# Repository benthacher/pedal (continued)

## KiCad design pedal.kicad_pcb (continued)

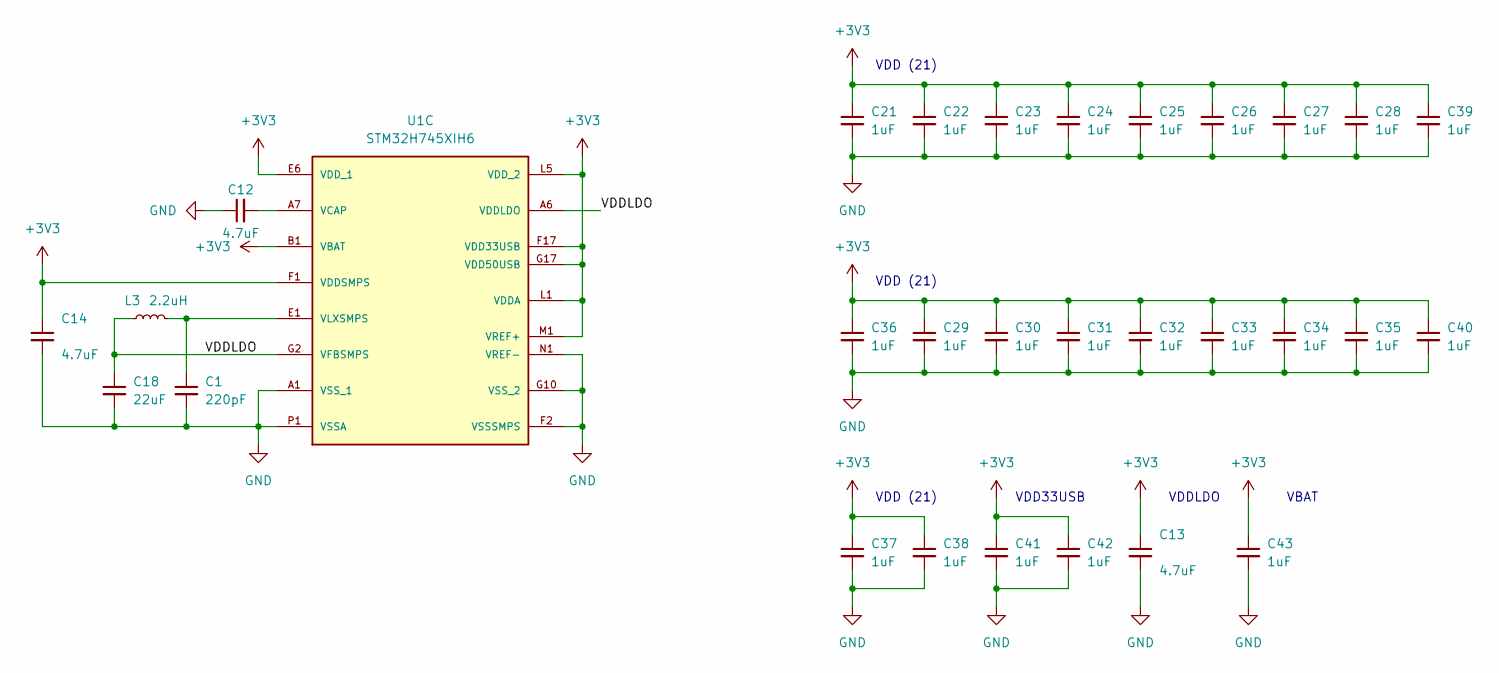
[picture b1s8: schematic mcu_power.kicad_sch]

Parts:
C1: 220pF; C_0402_1005Metric; Voltage 50V; LCSC C1530
C12, C13, C14: 4.7uF; C_0402_1005Metric; LCSC C23733
C18: 22uF; C_0805_2012Metric; Voltage 25V; LCSC C45783
C21, C22, C23, C24, C25, C26, C27, C28, C29, C30, C31, C32, C33, C34, C35, C36, C37, C38, C39, C40, C41, C42, C43: 1uF; C_0402_1005Metric; voltage 25; LCSC C52923
L3: 2.2uH; L_0805_2012Metric; LCSC C49435080
U1: STM32H745XIH6; BGA265C80P17X17_1400X1400X120; PARTREV 3; LCSC C1338373

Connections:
+3V3: C13.1, C14.1, C21.1, C22.1, C23.1, C24.1, C25.1, C26.1, C27.1, C28.1, C29.1, C30.1, C31.1, C32.1, C33.1, C34.1, C35.1, C36.1, C37.1, C38.1, C39.1, C40.1, C41.1, C42.1, C43.1, U1.B1 (VBAT), U1.E6 (VDD_1), U1.E9 (VDD_1), U1.E11 (VDD_1), U1.F1 (VDDSMPS), U1.F5 (VDD_1), U1.F17 (VDD33USB), U1.G5 (VDD_1), U1.G13 (VDD_1), U1.G17 (VDD50USB), U1.H5 (VDD_1), U1.H13 (VDD_1), U1.J13 (VDD_1), U1.K5 (VDD_1), U1.K13 (VDD_1), U1.L1 (VDDA), U1.L5 (VDD_2), U1.L13 (VDD_2), U1.M1 (VREF+), U1.M5 (VDD_2), U1.M13 (VDD_2), U1.N7 (VDD_2), U1.N8 (VDD_2), U1.N10 (VDD_2), U1.N11 (VDD_2), U1.N12 (VDD_2), U1.P17 (VDD_2); also elsewhere on the board
GND: C1.2, C12.1, C13.2, C14.2, C18.2, C21.2, C22.2, C23.2, C24.2, C25.2, C26.2, C27.2, C28.2, C29.2, C30.2, C31.2, C32.2, C33.2, C34.2, C35.2, C36.2, C37.2, C38.2, C39.2, C40.2, C41.2, C42.2, C43.2, U1.A1 (VSS_1), U1.A17 (VSS_1), U1.B2 (VSS_1), U1.B6 (VSS_1), U1.C10 (VSS_1), U1.C13 (VSS_1), U1.C16 (VSS_1), U1.F2 (VSSSMPS), U1.G7 (VSS_1), U1.G8 (VSS_1), U1.G9 (VSS_1), U1.G10 (VSS_2), U1.G11 (VSS_2), U1.G16 (VSS_1), U1.H7 (VSS_2), U1.H8 (VSS_2), U1.H9 (VSS_2), U1.H10 (VSS_2), U1.H11 (VSS_2), U1.J3 (VSS_1), U1.J7 (VSS_2), U1.J8 (VSS_2), U1.J9 (VSS_2), U1.J10 (VSS_2), U1.J11 (VSS_2), U1.J16 (VSS_1), U1.J17 (VSS_1), U1.K7 (VSS_2), U1.K8 (VSS_2), U1.K9 (VSS_2), U1.K10 (VSS_2), U1.K11 (VSS_2), U1.K15 (VSS_1), U1.L7 (VSS_2), U1.L8 (VSS_2), U1.L9 (VSS_2), U1.L10 (VSS_2), U1.L11 (VSS_2), U1.L15 (VSS_1), U1.M15 (VSS_1), U1.N1 (VREF-), U1.N16 (VSS_1), U1.P1 (VSSA), U1.R4 (VSS_1), U1.R8 (VSS_1), U1.T12 (VSS_1), U1.U1 (VSS_1), U1.U17 (VSS_1); also elsewhere on the board
unnamed: C1.1, L3.2, U1.E1 (VLXSMPS)
VCAP: C12.2, U1.A7 (VCAP), U1.D17 (VCAP), U1.U11 (VCAP)
VDDLDO: C18.1, L3.1, U1.A6 (VDDLDO), U1.C17 (VDDLDO), U1.G2 (VFBSMPS), U1.U12 (VDDLDO)

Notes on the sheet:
VDD33USB
VDD (21)
VDDLDO
VBAT

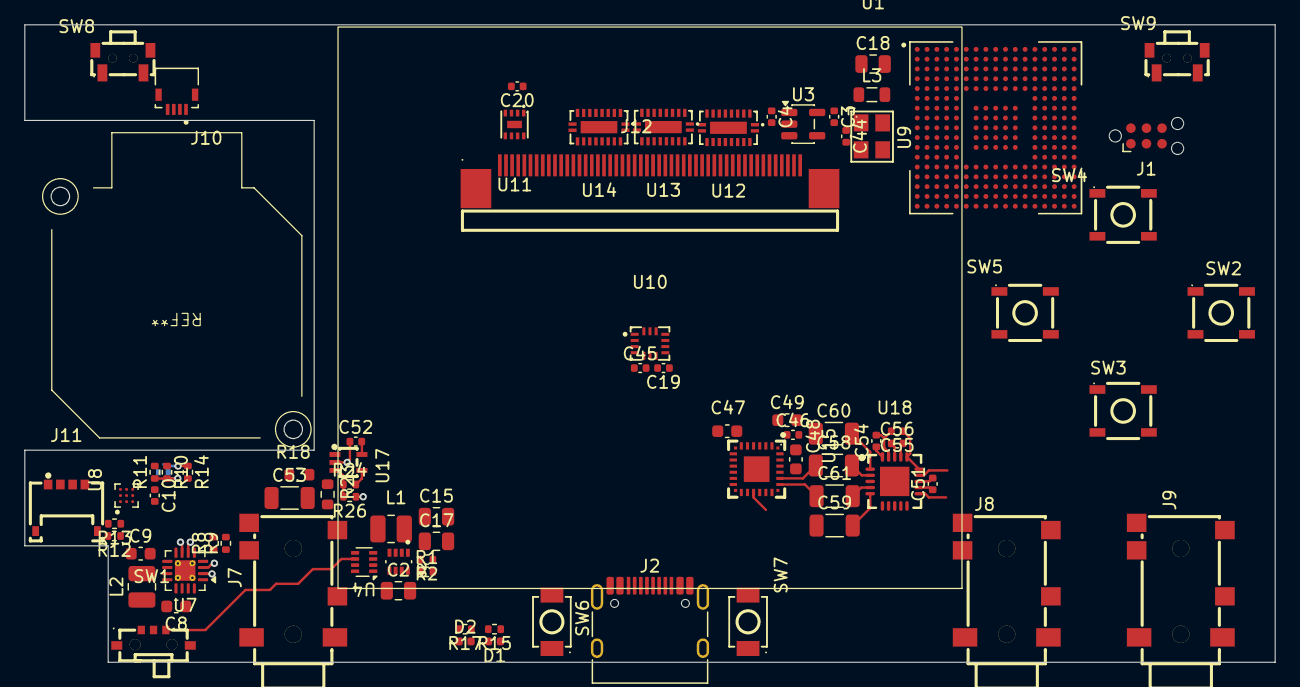
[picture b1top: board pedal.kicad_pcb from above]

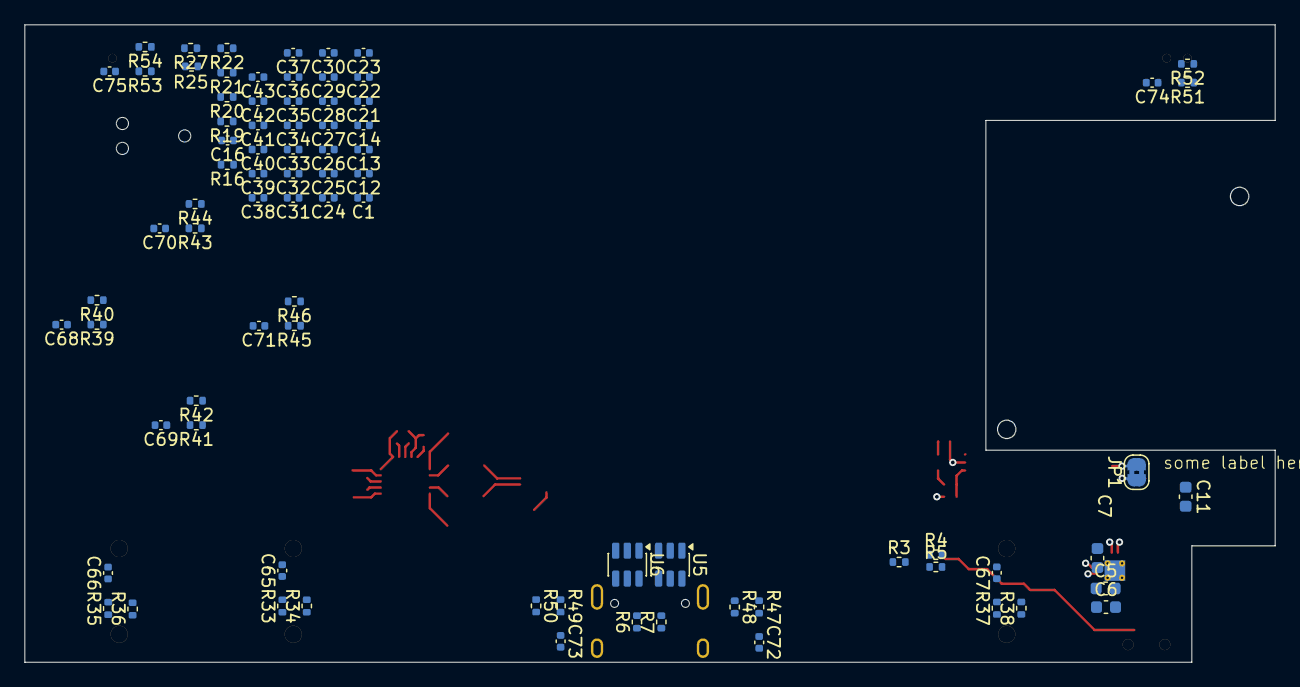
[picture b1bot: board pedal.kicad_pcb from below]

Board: 4 copper layers, 102.0 x 51.9 mm, 159 parts (80 on the bottom side), 156 nets.

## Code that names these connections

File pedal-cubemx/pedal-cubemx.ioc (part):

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Mcu.Name=STM32H745XIHx
Mcu.Package=TFBGA240
Mcu.UserName=STM32H745XIHx
PA11.GPIOParameters=PinAttribute
PA11.Mode=Device_Only
PA11.PinAttribute=CortexM4
PA11.Signal=USB_OTG_FS_DM
PA12.GPIOParameters=PinAttribute
PA12.Mode=Device_Only
PA12.PinAttribute=CortexM4
PA12.Signal=USB_OTG_FS_DP
PA13\ (JTMS/SWDIO).GPIOParameters=PinAttribute
PA13\ (JTMS/SWDIO).Mode=Trace_Asynchronous_SW
PA13\ (JTMS/SWDIO).PinAttribute=CortexM7
PA13\ (JTMS/SWDIO).Signal=DEBUG_JTMS-SWDIO
PA14\ (JTCK/SWCLK).GPIOParameters=PinAttribute
PA14\ (JTCK/SWCLK).Mode=Trace_Asynchronous_SW
PA14\ (JTCK/SWCLK).PinAttribute=CortexM7
PA14\ (JTCK/SWCLK).Signal=DEBUG_JTCK-SWCLK
PA3.GPIOParameters=PinAttribute
PA3.PinAttribute=CortexM4
PA3.Signal=ADCx_INP15
PA4.GPIOParameters=PinAttribute
PA4.PinAttribute=CortexM4
PA4.Signal=ADCx_INP18
PA5.GPIOParameters=GPIO_Label,PinAttribute
PA5.GPIO_Label=LED
PA5.PinAttribute=Free
PA5.Signal=GPIO_Output
PA8.GPIOParameters=PinAttribute
PA8.PinAttribute=CortexM4
PA8.Signal=S_TIM1_CH1
PB3\ (JTDO/TRACESWO).GPIOParameters=PinAttribute
PB3\ (JTDO/TRACESWO).Mode=Trace_Asynchronous_SW
PB3\ (JTDO/TRACESWO).PinAttribute=CortexM7
PB3\ (JTDO/TRACESWO).Signal=DEBUG_JTDO-SWO
PB5.GPIOParameters=PinAttribute
PB5.Mode=Full_Duplex_Master
PB5.PinAttribute=CortexM4
PB5.Signal=SPI1_MOSI
PB6.GPIOParameters=PinAttribute
PB6.Mode=I2C
PB6.PinAttribute=CortexM4
PB6.Signal=I2C1_SCL
PB7.GPIOParameters=PinAttribute
PB7.Mode=I2C
PB7.PinAttribute=CortexM4
PB7.Signal=I2C1_SDA
PC10.GPIOParameters=PinAttribute
PC10.Mode=Asynchronous
PC10.PinAttribute=CortexM4
PC10.Signal=UART4_TX
PC11.GPIOParameters=PinAttribute
PC11.Mode=Asynchronous
PC11.PinAttribute=CortexM4
PC11.Signal=UART4_RX
PC9.GPIOParameters=PinAttribute
PC9.Mode=I2C
PC9.PinAttribute=CortexM4
PC9.Signal=I2C3_SDA
PD0.GPIOParameters=PinAttribute
PD0.PinAttribute=CortexM4
PD0.Signal=FMC_D2_DA2
PD1.GPIOParameters=PinAttribute
PD1.PinAttribute=CortexM4
PD1.Signal=FMC_D3_DA3
PD10.GPIOParameters=PinAttribute
PD10.PinAttribute=CortexM4
PD10.Signal=FMC_D15_DA15
PD14.GPIOParameters=PinAttribute
PD14.PinAttribute=CortexM4
PD14.Signal=FMC_D0_DA0
PD15.GPIOParameters=PinAttribute
PD15.PinAttribute=CortexM4
PD15.Signal=FMC_D1_DA1
PD4.GPIOParameters=PinAttribute
PD4.PinAttribute=CortexM4
PD4.Signal=FMC_NOE
PD5.GPIOParameters=PinAttribute
PD5.PinAttribute=CortexM4
PD5.Signal=FMC_NWE
PD6.GPIOParameters=PinAttribute
PD6.Mode=SAI_A_Master
PD6.PinAttribute=CortexM7
PD6.Signal=SAI1_SD_A
PD7.GPIOParameters=PinAttribute
PD7.Mode=NorPsramChipSelect1_1
PD7.PinAttribute=CortexM4
PD7.Signal=FMC_NE1
PD8.GPIOParameters=PinAttribute
PD8.PinAttribute=CortexM4
PD8.Signal=FMC_D13_DA13
PD9.GPIOParameters=PinAttribute
PD9.PinAttribute=CortexM4
PD9.Signal=FMC_D14_DA14
PE0.GPIOParameters=PinAttribute
PE0.Mode=ExternalTrigger
PE0.PinAttribute=CortexM4
PE0.Signal=LPTIM1_ETR
PE10.GPIOParameters=PinAttribute
PE10.PinAttribute=CortexM4
PE10.Signal=FMC_D7_DA7
PE11.GPIOParameters=PinAttribute
PE11.PinAttribute=CortexM4
PE11.Signal=FMC_D8_DA8
PE12.GPIOParameters=PinAttribute
PE12.PinAttribute=CortexM4
PE12.Signal=FMC_D9_DA9
PE13.GPIOParameters=PinAttribute
PE13.PinAttribute=CortexM4
PE13.Signal=FMC_D10_DA10
PE14.GPIOParameters=PinAttribute
PE14.PinAttribute=CortexM4
PE14.Signal=FMC_D11_DA11
PE15.GPIOParameters=PinAttribute
PE15.PinAttribute=CortexM4
PE15.Signal=FMC_D12_DA12
PE3.GPIOParameters=PinAttribute
PE3.Mode=SAI_B_SyncSlave
PE3.PinAttribute=CortexM7
PE3.Signal=SAI1_SD_B
PE4.GPIOParameters=PinAttribute
PE4.Mode=SAI_A_Master
PE4.PinAttribute=CortexM7
PE4.Signal=SAI1_FS_A
PE5.GPIOParameters=PinAttribute
PE5.Mode=SAI_A_Master
PE5.PinAttribute=CortexM7
PE5.Signal=SAI1_SCK_A
PE7.GPIOParameters=PinAttribute
PE7.PinAttribute=CortexM4
PE7.Signal=FMC_D4_DA4
PE8.GPIOParameters=PinAttribute
PE8.PinAttribute=CortexM4
PE8.Signal=FMC_D5_DA5
PE9.GPIOParameters=PinAttribute
PE9.PinAttribute=CortexM4
PE9.Signal=FMC_D6_DA6
PF1.GPIOParameters=PinAttribute
PF1.Mode=I2C
PF1.PinAttribute=CortexM4
PF1.Signal=I2C2_SCL
PF4.GPIOParameters=PinAttribute
PF4.PinAttribute=CortexM4
PF4.Signal=FMC_A4
PG10.GPIOParameters=PinAttribute
PG10.Mode=NSS_Signal_Hard_Output
PG10.PinAttribute=CortexM4
PG10.Signal=SPI1_NSS
PG11.GPIOParameters=PinAttribute
PG11.Mode=Full_Duplex_Master
PG11.PinAttribute=CortexM4
PG11.Signal=SPI1_SCK
PG9.GPIOParameters=PinAttribute
PG9.Mode=Full_Duplex_Master
PG9.PinAttribute=CortexM4
PG9.Signal=SPI1_MISO
PH0-OSC_IN\ (PH0).GPIOParameters=PinAttribute
PH0-OSC_IN\ (PH0).Mode=HSE-External-Clock-Source
PH0-OSC_IN\ (PH0).PinAttribute=Free
PH0-OSC_IN\ (PH0).Signal=RCC_OSC_IN
PH5.GPIOParameters=PinAttribute
PH5.Mode=I2C
PH5.PinAttribute=CortexM4
PH5.Signal=I2C2_SDA
PH7.GPIOParameters=PinAttribute
PH7.Mode=I2C
PH7.PinAttribute=CortexM4
PH7.Signal=I2C3_SCL
PI0.GPIOParameters=PinAttribute
PI0.PinAttribute=Free
PI0.Signal=GPIO_Output
PI1.GPIOParameters=PinAttribute
PI1.PinAttribute=Free
PI1.Signal=GPIO_Output
PI2.GPIOParameters=PinAttribute
PI2.PinAttribute=Free
PI2.Signal=GPIO_Output
PI3.GPIOParameters=PinAttribute
PI3.PinAttribute=Free
PI3.Signal=GPIO_Output
PI4.GPIOParameters=PinAttribute
PI4.PinAttribute=Free
PI4.Signal=GPIO_Output
PI5.GPIOParameters=PinAttribute
PI5.PinAttribute=Free
PI5.Signal=GPIO_Output
PJ1.GPIOParameters=PinAttribute
PJ1.PinAttribute=Free
PJ1.Signal=GPXTI1
PJ10.GPIOParameters=PinAttribute
PJ10.PinAttribute=Free
PJ10.Signal=GPXTI10
PJ11.GPIOParameters=PinAttribute
PJ11.PinAttribute=Free
PJ11.Signal=GPXTI11
PJ12.GPIOParameters=PinAttribute
PJ12.PinAttribute=Free
PJ12.Signal=GPXTI12
PJ2.GPIOParameters=PinAttribute
PJ2.PinAttribute=Free
PJ2.Signal=GPXTI2
PJ3.GPIOParameters=PinAttribute
PJ3.PinAttribute=Free
PJ3.Signal=GPXTI3
PJ4.GPIOParameters=PinAttribute
PJ4.PinAttribute=Free
PJ4.Signal=GPXTI4
PJ5.GPIOParameters=PinAttribute
PJ5.PinAttribute=Free
PJ5.Signal=GPXTI5
PJ6.GPIOParameters=PinAttribute
PJ6.PinAttribute=Free
PJ6.Signal=GPXTI6
PJ7.GPIOParameters=PinAttribute
PJ7.PinAttribute=Free
PJ7.Signal=GPXTI7
PJ8.GPIOParameters=PinAttribute
PJ8.PinAttribute=Free
PJ8.Signal=GPXTI8
PJ9.GPIOParameters=PinAttribute
PJ9.PinAttribute=Free
PJ9.Signal=GPXTI9
RCC.SYSCLKFreq_VALUE=64000000
board=custom

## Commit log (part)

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2026-04-25 Added microcontroller and custom symbol library
2026-04-25 Added microcontroller subsheet, gitignore updates
2026-04-25 add power path sheet
2026-04-25 buck boost regulator schematic done
2026-04-25 fixed microcontroller footprint
2026-04-25 Added TPS631000
2026-04-25 add-symbol.py now removes symbol files
2026-04-25 added LDO for LCD rail
2026-04-25 add tps2121 power mux component
2026-04-25 saved everything
2026-04-29 remove tps2121
2026-04-30 fix removing merged library files
2026-04-30 random silly commit
2026-04-30 add type c receptacle
2026-04-30 add esd protection to usb port
2026-04-30 add bq25302 charger
2026-04-30 charger supporting circuitry
2026-04-30 add fuel gauge
2026-04-30 fix fuel gauge symbol pins
2026-04-30 fuel gauge wip
2026-05-07 add switch for 3V3 enable
2026-05-10 vbatt is switched into power mux
2026-05-10 add switch model
2026-05-10 add pull up/down to fuel gauge
2026-05-10 LDO NC pin to ground
2026-05-10 formatting
2026-05-19 add display footprint
2026-05-19 embed 3d model for fuel gauge in footprint
2026-05-19 add switch switch to user drawings
2026-05-19 random changes
2026-05-30 rename custom libraries to custom, add easyeda2kicad integration
2026-05-30 embed all 3d models
2026-05-30 move switch to be on grid
2026-05-30 move stuff a bit
2026-06-05 add thermistor biasing resistors
2026-06-05 add battery connector
2026-06-05 update fast charge current
2026-06-05 update pcb
2026-06-05 add battery connector model and charge led
2026-06-05 replace battery connector with solder pads
2026-06-05 Power path (#1)
    * add power path sheet
    * Added TPS631000
    * add-symbol.py now removes symbol files
    * fixed microcontroller footprint
    * buck boost regulator schematic done
    * added LDO for LCD rail
2026-06-05 add pedal cubemx file
2026-06-05 add microcontroller decoupling
2026-06-06 add decoupling caps
2026-06-06 fix footprints and add smps
2026-06-06 add user led
2026-06-06 add usb
2026-06-12 add debug pins
2026-06-12 add fmc pins, stomp uart, fuel gauge i2c
2026-06-12 update ioc
2026-06-12 add a bunch of peripherals
2026-06-12 add all external signals
2026-06-12 add no connects
2026-06-12 add oscillator
2026-06-12 MCU (#2)
    * add pedal cubemx file
    * add microcontroller decoupling
    * add decoupling caps
    * fix footprints and add smps
    * add user led
    * add usb
2026-06-16 add imu sheet and library
2026-06-16 fix up routing between sheets
2026-06-16 IMU (#3)
    * add imu sheet and library
    * routing between sheets
2026-06-16 add lcd backlight driver, hierarchical signals to display page
2026-06-16 update ioc with backlight signals
